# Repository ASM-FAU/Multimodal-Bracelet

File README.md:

# Multimodal-Bracelet
This project provides electrical and mechanical plans such as all software to build a multimodal bracelet that can be used to acquire muscular activity. The bracelet is designed around the commercial Avanti Trigno EMG sensors by Delsys. We combine each EMG sensor with 4 FMG sensors (FSRs). That way each module can acquire EMG and IMU data by the Avanti Trigno sensors and FMG. The following Figure shows how we combined the multiple modalities in a single module.

The following Figre shows a rough outline of the PCB layout which are provided within this project.

The pictures below shall help to get a better understanding about the design of the bracelet and shall help when replicating the device.

<p align="center">

  <br>

</p>

<p align="center">

  <br>

</p>

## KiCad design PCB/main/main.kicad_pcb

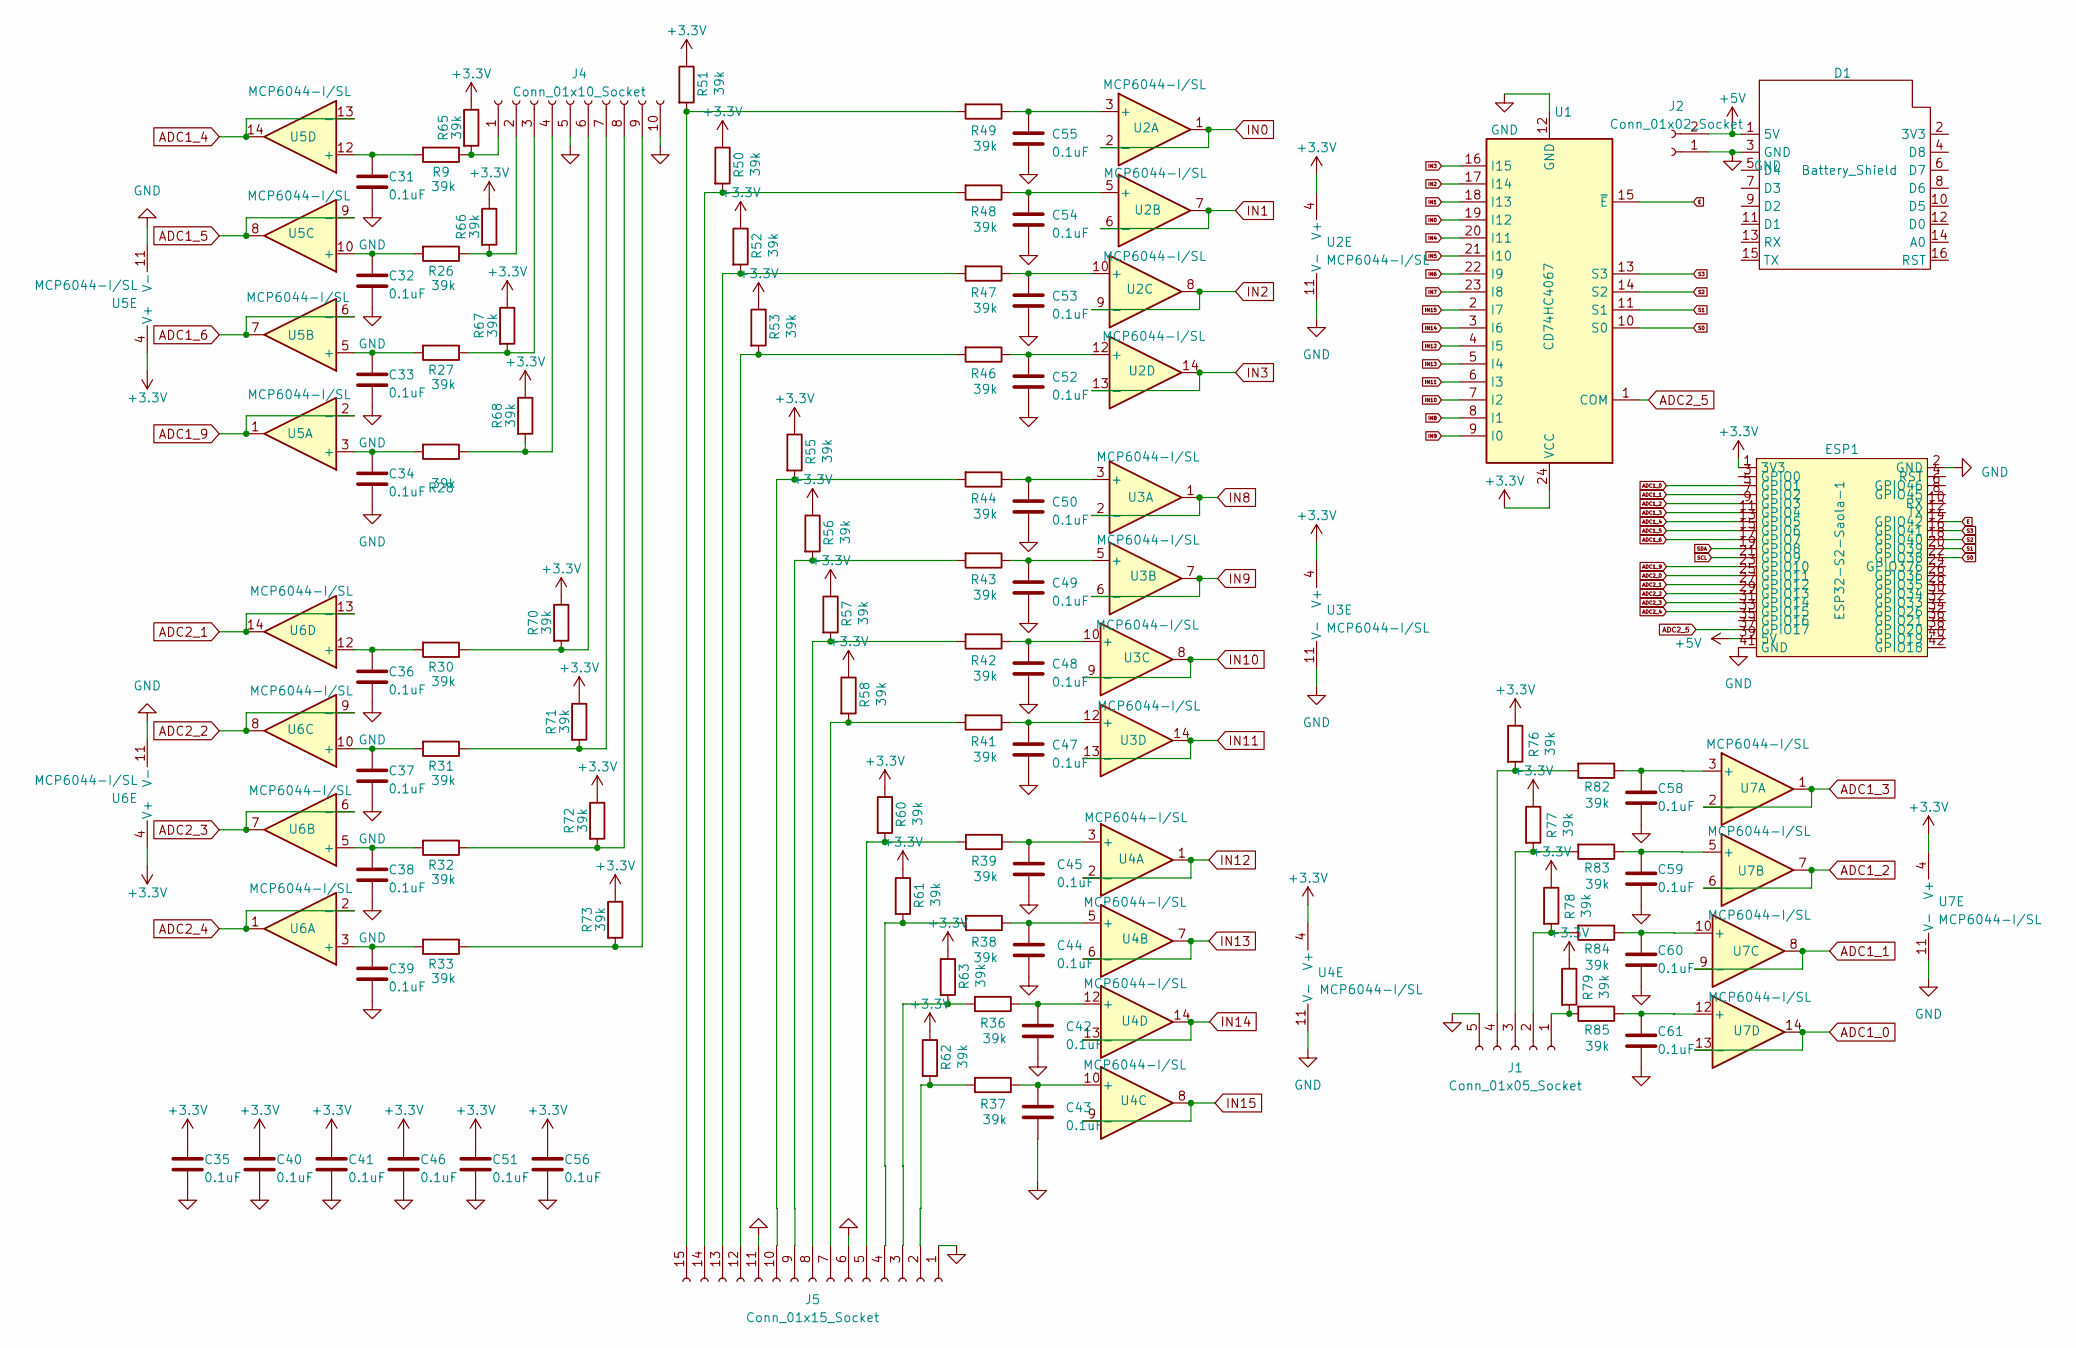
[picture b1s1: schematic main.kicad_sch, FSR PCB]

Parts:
C31, C32, C33, C34, C35, C36, C37, C38, C39, C40, C41, C42, C43, C44, C45, C46, C47, C48, C49, C50, C51, C52, C53, C54, C55, C56, C58, C59, C60, C61: 0.1uF; C_0603_1608Metric_Pad1.08x0.95mm_HandSolder; MFR Part CL10A104KA8NNNC; JLCPCB Part C2762593
D1: Battery_Shield; Battery Shield
ESP1: ESP32-S2-Saola-1
J1: Conn_01x05_Socket; PinSocket_1x05_P2.54mm_Vertical
J2: Conn_01x02_Socket; PinSocket_1x02_P2.54mm_Vertical
J4: Conn_01x10_Socket; PinSocket_1x10_P2.54mm_Vertical
J5: Conn_01x15_Socket; PinSocket_1x15_P2.54mm_Vertical
R9, R26, R27, R28, R30, R31, R32, R33, R36, R37, R38, R39, R41, R42, R43, R44, R46, R47, R48, R49, R50, R51, R52, R53, R55, R56, R57, R58, R60, R61, R62, R63, R65, R66, R67, R68, R70, R71, R72, R73, R76, R77, R78, R79, R82, R83, R84, R85: 39k; R_0603_1608Metric_Pad0.98x0.95mm_HandSolder; MFR Part ES03W4F3902T5E; JLCPCB Part C2772794
U1: CD74HC4067; SOIC-24W_7.5x15.4mm_P1.27mm; MFR Part CD74HC4067M; JLCPCB Part C1545936
U2, U3, U4, U5, U6, U7: MCP6044-I/SL; MCP6044ISL; MFR Part MCP6044-I/SL; JLCPCB Part C50260

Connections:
+3.3V: C35.1, C40.1, C41.1, C46.1, C51.1, C56.1, ESP1.1 (3V3), R50.1, R51.1, R52.1, R53.1, R55.1, R56.1, R57.1, R58.1, R60.1, R61.1, R62.1, R63.1, R65.1, R66.1, R67.1, R68.1, R70.1, R71.1, R72.1, R73.1, R76.1, R77.1, R78.1, R79.1, U1.24 (VCC), U2.4 (V+), U3.4 (V+), U4.4 (V+), U5.4 (V+), U6.4 (V+), U7.4 (V+)
+5V: D1.1 (5V), ESP1.39 (5V), J2.2
ADC1_0: ESP1.5 (GPIO1), U7.13 (-), U7.14
ADC1_1: ESP1.7 (GPIO2), U7.8, U7.9 (-)
ADC1_2: ESP1.9 (GPIO3), U7.6 (-), U7.7
ADC1_3: ESP1.11 (GPIO4), U7.1, U7.2 (-)
ADC1_4: ESP1.13 (GPIO5), U5.13 (-), U5.14
ADC1_5: ESP1.15 (GPIO6), U5.8, U5.9 (-)
ADC1_6: ESP1.17 (GPIO7), U5.6 (-), U5.7
ADC1_9: ESP1.23 (GPIO10), U5.1, U5.2 (-)
ADC2_0: ESP1.25 (GPIO11)
ADC2_1: ESP1.27 (GPIO12), U6.13 (-), U6.14
ADC2_2: ESP1.29 (GPIO13), U6.8, U6.9 (-)
ADC2_3: ESP1.31 (GPIO14), U6.6 (-), U6.7
ADC2_4: ESP1.33 (GPIO15), U6.1, U6.2 (-)
ADC2_5: ESP1.37 (GPIO17), U1.1 (COM)
E: ESP1.14 (GPIO42), U1.15 (~E)
GND: C31.2, C32.2, C33.2, C34.2, C35.2, C36.2, C37.2, C38.2, C39.2, C40.2, C41.2, C42.2, C43.2, C44.2, C45.2, C46.2, C47.2, C48.2, C49.2, C50.2, C51.2, C52.2, C53.2, C54.2, C55.2, C56.2, C58.2, C59.2, C60.2, C61.2, D1.3 (GND), ESP1.2 (GND), ESP1.41 (GND), J1.5, J2.1, J4.5, J4.10, J5.1, J5.6, J5.11, U1.12 (GND), U2.11 (V-), U3.11 (V-), U4.11 (V-), U5.11 (V-), U6.11 (V-), U7.11 (V-)
IN0: U1.19 (I12), U2.1, U2.2 (-)
IN1: U1.18 (I13), U2.6 (-), U2.7
IN2: U1.17 (I14), U2.8, U2.9 (-)
IN3: U1.16 (I15), U2.13 (-), U2.14
IN4: U1.20 (I11)
IN5: U1.21 (I10)
IN6: U1.22 (I9)
IN7: U1.23 (I8)
IN8: U1.8 (I1), U3.1, U3.2 (-)
IN9: U1.9 (I0), U3.6 (-), U3.7
IN10: U1.7 (I2), U3.8, U3.9 (-)
IN11: U1.6 (I3), U3.13 (-), U3.14
IN12: U1.4 (I5), U4.1, U4.2 (-)
IN13: U1.5 (I4), U4.6 (-), U4.7
IN14: U1.3 (I6), U4.13 (-), U4.14
IN15: U1.2 (I7), U4.8, U4.9 (-)
unnamed: J1.1, R79.2, R85.2
unnamed: J1.2, R78.2, R84.2
unnamed: J1.3, R77.2, R83.2
unnamed: J1.4, R76.2, R82.2
unnamed: J4.1, R9.1, R65.2
unnamed: J4.2, R26.1, R66.2
unnamed: J4.3, R27.1, R67.2
unnamed: J4.4, R28.1, R68.2
unnamed: J4.6, R30.1, R70.2
unnamed: J4.7, R31.1, R71.2
unnamed: J4.8, R32.1, R72.2
unnamed: J4.9, R33.1, R73.2
unnamed: J5.2, R37.2, R62.2
unnamed: J5.3, R36.2, R63.2
unnamed: J5.4, R38.2, R61.2
unnamed: J5.5, R39.2, R60.2
unnamed: J5.7, R41.2, R58.2
unnamed: J5.8, R42.2, R57.2
unnamed: J5.9, R43.2, R56.2
unnamed: J5.10, R44.2, R55.2
unnamed: J5.12, R46.2, R53.2
unnamed: J5.13, R47.2, R52.2
unnamed: J5.14, R48.2, R50.2
unnamed: J5.15, R49.2, R51.2
unnamed: C55.1, R49.1, U2.3 (+)
unnamed: C54.1, R48.1, U2.5 (+)
unnamed: C53.1, R47.1, U2.10 (+)
unnamed: C52.1, R46.1, U2.12 (+)
unnamed: C50.1, R44.1, U3.3 (+)
unnamed: C49.1, R43.1, U3.5 (+)
unnamed: C48.1, R42.1, U3.10 (+)
unnamed: C47.1, R41.1, U3.12 (+)
unnamed: C45.1, R39.1, U4.3 (+)
unnamed: C44.1, R38.1, U4.5 (+)
unnamed: C43.1, R37.1, U4.10 (+)
unnamed: C42.1, R36.1, U4.12 (+)
unnamed: C34.1, R28.2, U5.3 (+)
unnamed: C33.1, R27.2, U5.5 (+)
unnamed: C32.1, R26.2, U5.10 (+)
unnamed: C31.1, R9.2, U5.12 (+)
unnamed: C39.1, R33.2, U6.3 (+)
unnamed: C38.1, R32.2, U6.5 (+)
unnamed: C37.1, R31.2, U6.10 (+)
unnamed: C36.1, R30.2, U6.12 (+)
unnamed: C58.1, R82.1, U7.3 (+)
unnamed: C59.1, R83.1, U7.5 (+)
unnamed: C60.1, R84.1, U7.10 (+)
unnamed: C61.1, R85.1, U7.12 (+)
S0: ESP1.22 (GPIO38), U1.10 (S0)
S1: ESP1.20 (GPIO39), U1.11 (S1)
S2: ESP1.18 (GPIO40), U1.14 (S2)
S3: ESP1.16 (GPIO41), U1.13 (S3)
SCL: ESP1.21 (GPIO9)
SDA: ESP1.19 (GPIO8)

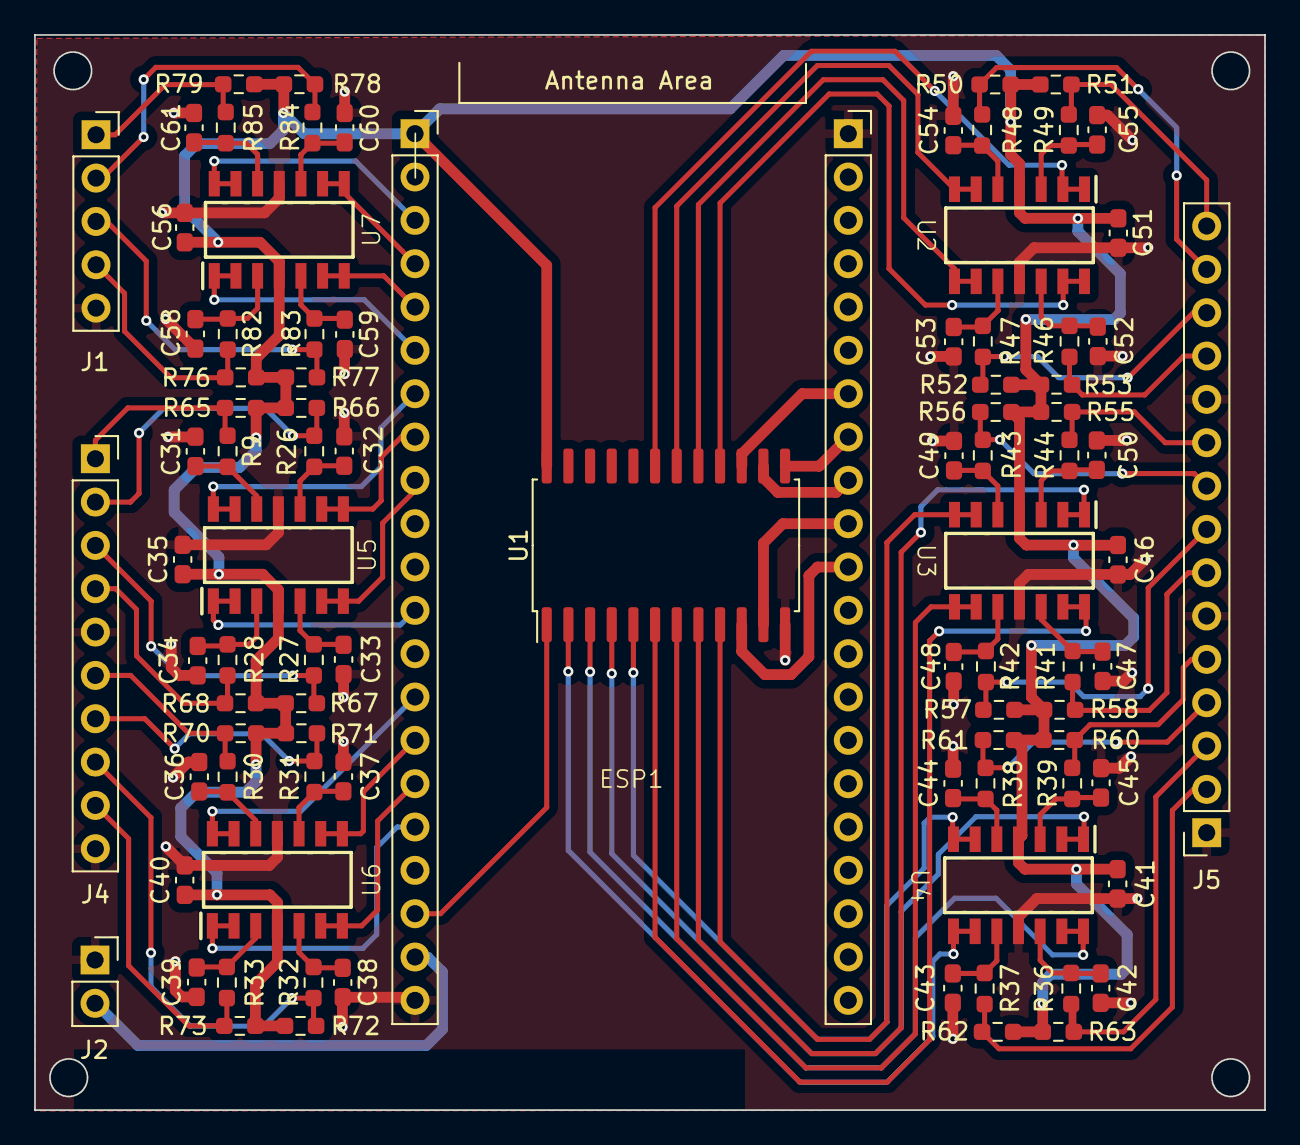
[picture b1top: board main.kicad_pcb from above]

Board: 2 copper layers, 72.1 x 63.0 mm, 90 parts (0 on the bottom side), 81 nets.

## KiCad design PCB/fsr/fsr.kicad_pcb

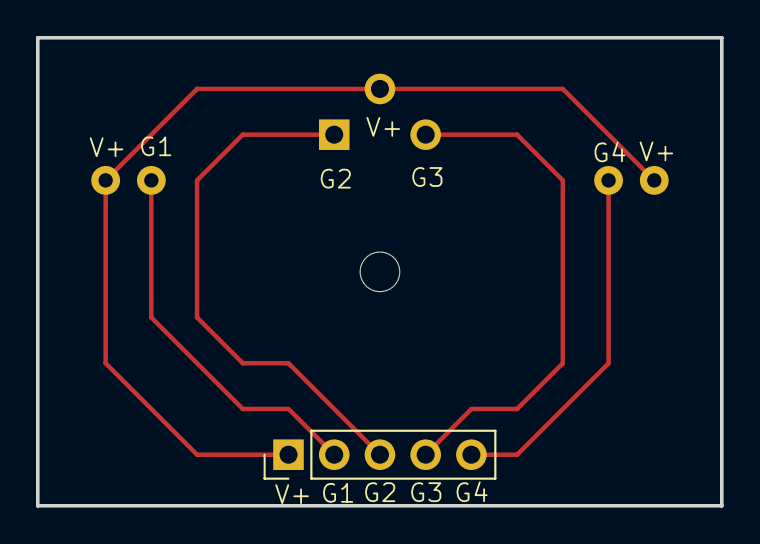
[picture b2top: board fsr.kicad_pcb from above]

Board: 2 copper layers, 38.0 x 26.0 mm, 5 parts (0 on the bottom side), 5 nets.

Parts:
H1: MountingHole; MountingHole_2.2mm_M2
J1: Conn_01x05; PinHeader_1x05_P2.54mm_Vertical
J5: Conn_01x03_Pin; PinHeader_1x03_P2.54mm_Vertical
R1, R4: R; R_LDR_4.9x4.2mm_P2.54mm_Vertical

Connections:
unnamed: J1.1, J5.2, R1.1, R4.2
unnamed: J1.2, R1.2
unnamed: J1.3, J5.1
unnamed: J1.4, J5.3
unnamed: J1.5, R4.1

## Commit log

2024-08-16 Update README.md
    added images
2025-01-27 main: Added updated version 2 with better tolerances and less screws
